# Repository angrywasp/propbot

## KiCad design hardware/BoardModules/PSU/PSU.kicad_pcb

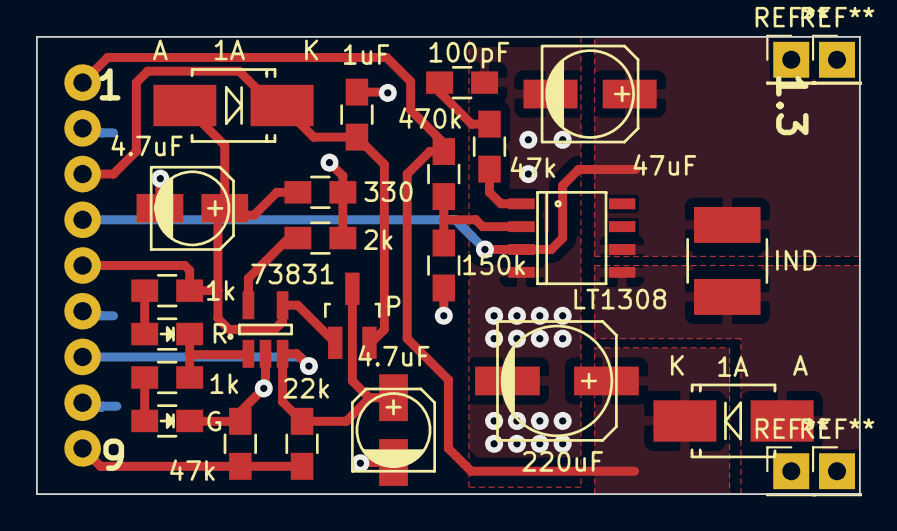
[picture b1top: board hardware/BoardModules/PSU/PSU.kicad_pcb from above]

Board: 2 copper layers, 45.7 x 25.4 mm, 27 parts (0 on the bottom side), 15 nets.

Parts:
C1, C3: 4.7uF; 4x5.3
C2: 1uF; 0805_HS
C4: 47uF; 5x5.8
C5: 100pF; 0805_HS
C6: 220uF; 6.3x7.7
D1, D2: 1A; SMB_HS
L1: IND; NR4018_HandSoldering
LED1: R; LED_0805_HS
LED2: G; LED_0805_HS
P1: INPUT; Pin_Header_Circular_1x02
P2: CONN_01X03; Pin_Header_Circular_1x03
P3: PWR_SW; Pin_Header_Circular_1x02
P4: OUTPUT; Pin_Header_Circular_1x02
Q1: P; SOT-23_HS
R1, R2: 1k; 0805_HS
R3: 2k; 0805_HS
R4: 330; 0805_HS
R5, R9: 47k; 0805_HS
R6: 150k; 0805_HS
R7: 470k; 0805_HS
R8: 22k; 0805_HS
U1: 73831; SOT-23-5_HS
U2: LT1308; SO-8

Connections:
GND: C1.2, C2.2, C3.2, C4.2, C5.2, C6.2, LED2.1, P1.2, P2.2, P4.1, R3.2, R4.1, R6.2, R9.2, U1.2, U2.4
unnamed: C1.1, D1.2, P1.1, Q1.1, R1.1, R4.2, U1.4
unnamed: C2.1, D1.1, P3.1, Q1.2
unnamed: C3.1, P2.3, Q1.3, R8.2, U1.3
unnamed: C4.1, L1.1, P3.2, U2.3, U2.6
unnamed: C5.1, R5.2
unnamed: C6.1, D2.1, P4.2, R7.1
unnamed: D2.2, L1.2, U2.5
unnamed: LED1.1, R2.1, U1.1
unnamed: LED1.2, R1.2
unnamed: LED2.2, R2.2
unnamed: P2.1, R8.1, R9.1
unnamed: R3.1, U1.5
unnamed: R5.1, U2.1
unnamed: R6.1, R7.2, U2.2

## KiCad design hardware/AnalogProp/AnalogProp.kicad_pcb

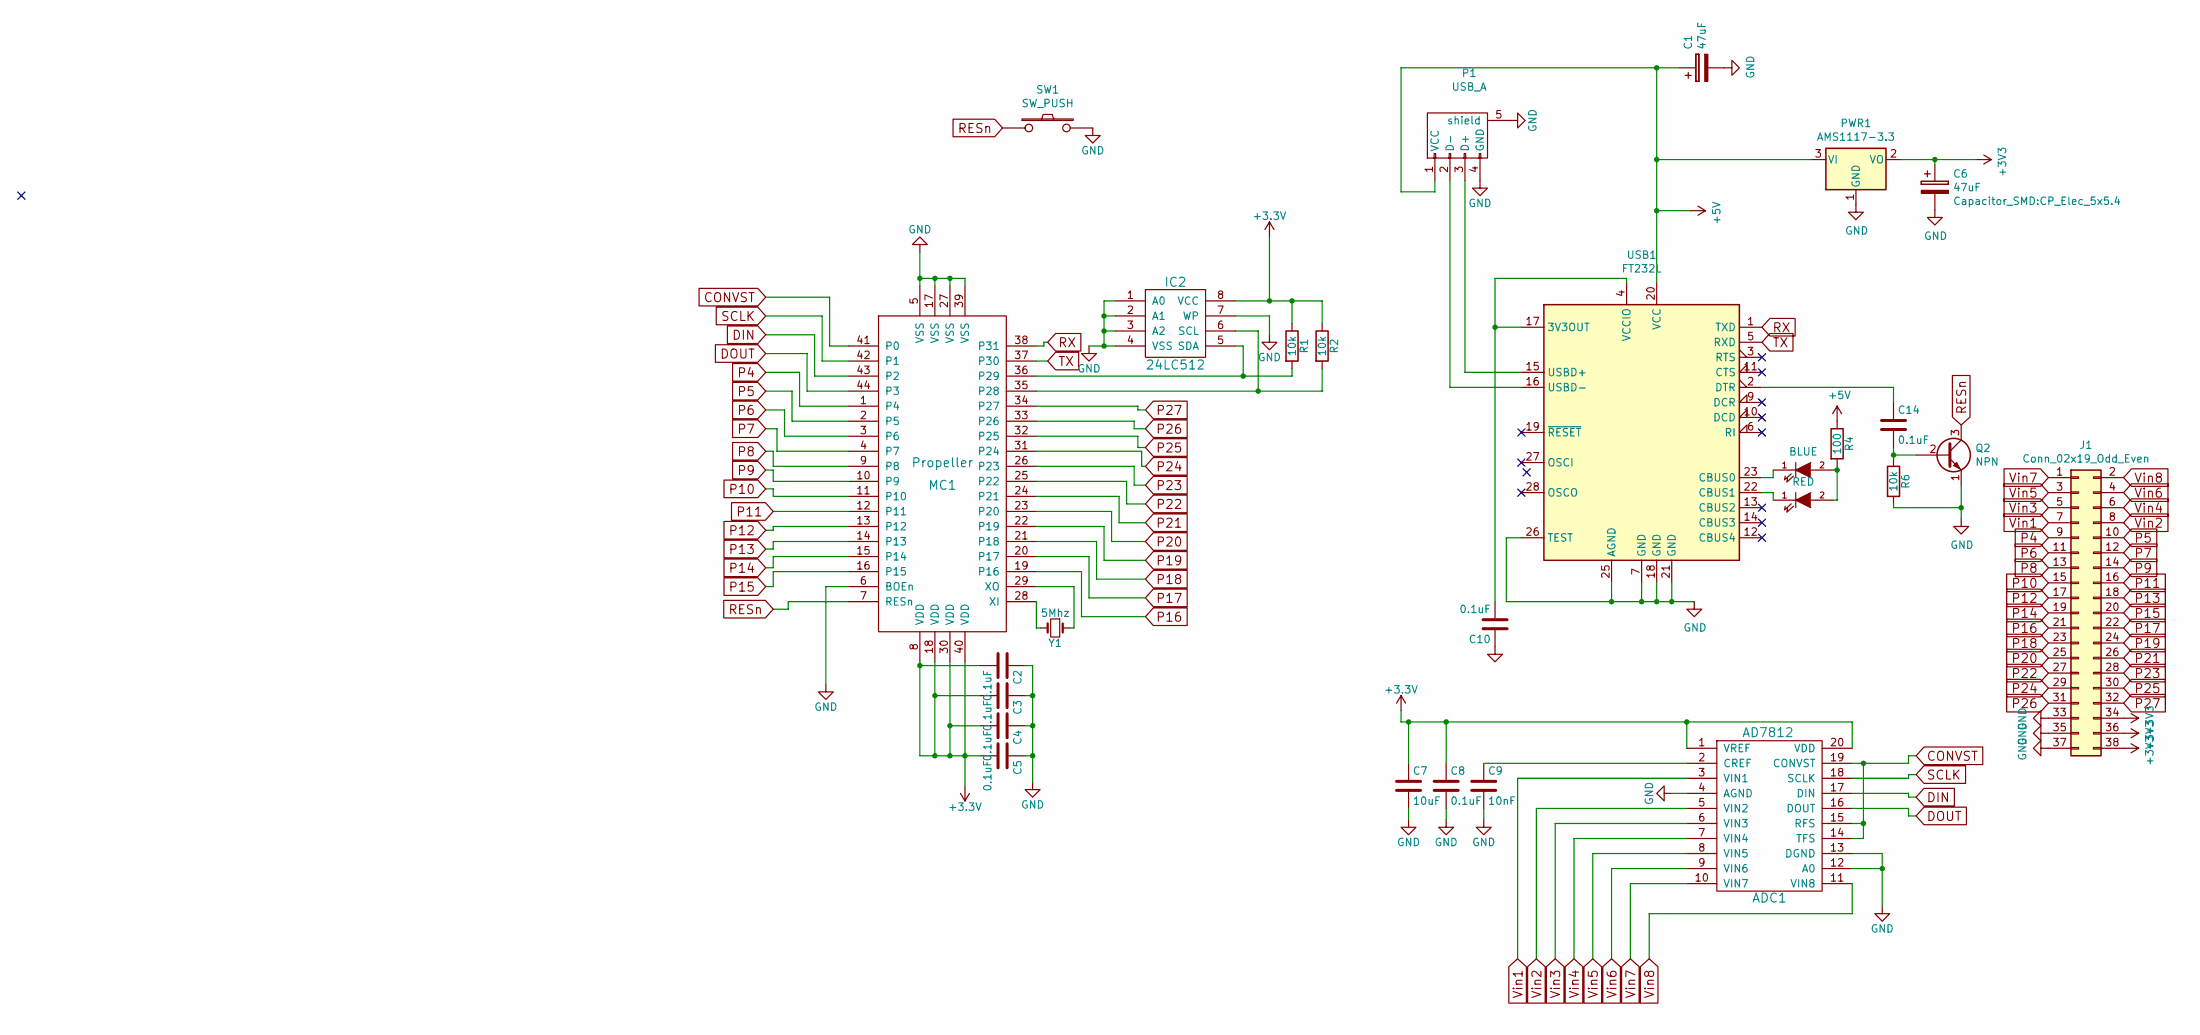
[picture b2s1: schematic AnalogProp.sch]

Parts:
ADC1: AD7812
C1, C6: 47uF; CP_Elec_5x5.4
C2, C3, C4, C5, C8, C10, C14: 0.1uF; 0805_HS
C7: 10uF; 0805_HS
C9: 10nF; 0805_HS
D2: BLUE; LED_0805_HS
D3: RED; LED_0805_HS
IC2: 24LC512; 24LC512-W
J1: Conn_02x19_Odd_Even; PinSocket_2x19_P2.54mm_Vertical
MC1: Propeller; P8X32A
P1: USB_A; USB_A_CNCTech_1001-011-01101_Horizontal
PWR1: AMS1117-3.3; SOT-223
Q2: NPN; SOT-23_HS
R1, R2, R6: 10k; 0805_HS
R4: 100; 0805_HS
SW1: SW_PUSH; SW_SPST
USB1: FT232L; SSOP-28_5.3x10.2mm_P0.65mm
Y1: 5Mhz; XTAL-2

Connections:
+5V: C1.1, P1.1 (VCC), PWR1.3 (VI), R4.1, USB1.20 (VCC); also elsewhere on the board
CONVST: ADC1.14 (TFS), ADC1.15 (RFS), ADC1.19 (CONVST), MC1.41 (P0)
DIN: ADC1.17 (DIN), MC1.43 (P2)
DOUT: ADC1.16 (DOUT), MC1.44 (P3)
GND: ADC1.4 (AGND), ADC1.12 (A0), ADC1.13 (DGND), C1.2, C2.1, C3.1, C4.1, C5.1, C6.2, C7.2, C8.2, C9.2, C10.1, IC2.1 (A0), IC2.2 (A1), IC2.3 (A2), IC2.4 (VSS), IC2.7 (WP), J1.33, J1.35, J1.37, MC1.5 (VSS), MC1.6 (BOEn), MC1.17 (VSS), MC1.27 (VSS), MC1.39 (VSS), P1.4 (GND), P1.5 (shield), PWR1.1 (GND), Q2.1 (E), R6.2, SW1.2, USB1.7 (GND), USB1.18 (GND), USB1.21 (GND), USB1.25 (AGND), USB1.26 (TEST); also elsewhere on the board
unnamed: ADC1.2 (CREF), C9.1
unnamed: C10.2, USB1.4 (VCCIO), USB1.17 (3V3OUT)
unnamed: C14.1, USB1.2 (DTR)
unnamed: C14.2, Q2.2 (B), R6.1
unnamed: D2.1 (K), USB1.23 (CBUS0)
unnamed: D2.2 (A), D3.2 (A), R4.2
unnamed: D3.1 (K), USB1.22 (CBUS1)
unnamed: IC2.5 (SDA), MC1.36 (P29), R1.2
unnamed: IC2.6 (SCL), MC1.35 (P28), R2.2
unnamed: MC1.28 (XI), Y1.2
unnamed: MC1.29 (XO), Y1.1
unnamed 16: P1.2 (D-), USB1.16 (USBD-); also elsewhere on the board
unnamed 17: P1.3 (D+), USB1.15 (USBD+); also elsewhere on the board
P4: J1.9, MC1.1 (P4)
P5: J1.10, MC1.2 (P5)
P6: J1.11, MC1.3 (P6)
P7: J1.12, MC1.4 (P7)
P8: J1.13, MC1.9 (P8)
P9: J1.14, MC1.10 (P9)
P10: J1.15, MC1.11 (P10)
P11: J1.16, MC1.12 (P11)
P12: J1.17, MC1.13 (P12)
P13: J1.18, MC1.14 (P13)
P14: J1.19, MC1.15 (P14)
P15: J1.20, MC1.16 (P15)
P16: J1.21, MC1.19 (P16)
P17: J1.22, MC1.20 (P17)
P18: J1.23, MC1.21 (P18)
P19: J1.24, MC1.22 (P19)
P20: J1.25, MC1.23 (P20)
P21: J1.26, MC1.24 (P21)
P22: J1.27, MC1.25 (P22)
P23: J1.28, MC1.26 (P23)
P24: J1.29, MC1.31 (P24)
P25: J1.30, MC1.32 (P25)
P26: J1.31, MC1.33 (P26)
P27: J1.32, MC1.34 (P27)
RESn: MC1.7 (RESn), Q2.3 (C), SW1.1
RX: MC1.38 (P31), USB1.1 (TXD)
SCLK: ADC1.18 (SCLK), MC1.42 (P1)
TX: MC1.37 (P30), USB1.5 (RXD)
Vin1: ADC1.3 (VIN1), J1.7
Vin2: ADC1.5 (VIN2), J1.8
Vin3: ADC1.6 (VIN3), J1.5
Vin4: ADC1.7 (VIN4), J1.6
Vin5: ADC1.8 (VIN5), J1.3
Vin6: ADC1.9 (VIN6), J1.4
Vin7: ADC1.10 (VIN7), J1.1
Vin8: ADC1.11 (VIN8), J1.2

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
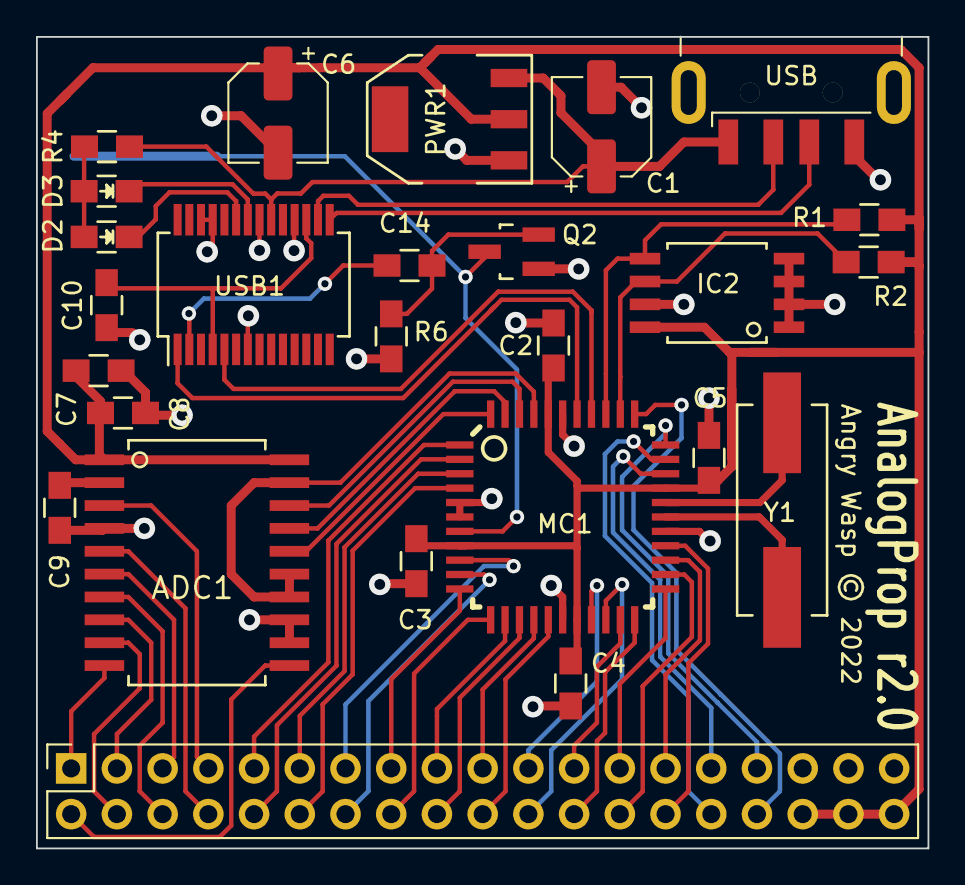
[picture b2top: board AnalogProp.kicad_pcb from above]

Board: 2 copper layers, 49.5 x 45.1 mm, 27 parts (1 on the bottom side), 55 nets.

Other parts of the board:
USB: USB_A; USB_A_CNCTech_1001-011-01101_Horizontal

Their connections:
+5V: USB.1; also elsewhere on the board
GND: USB.4, USB.5; also elsewhere on the board
unnamed 16: USB.2; also elsewhere on the board
unnamed 17: USB.3; also elsewhere on the board

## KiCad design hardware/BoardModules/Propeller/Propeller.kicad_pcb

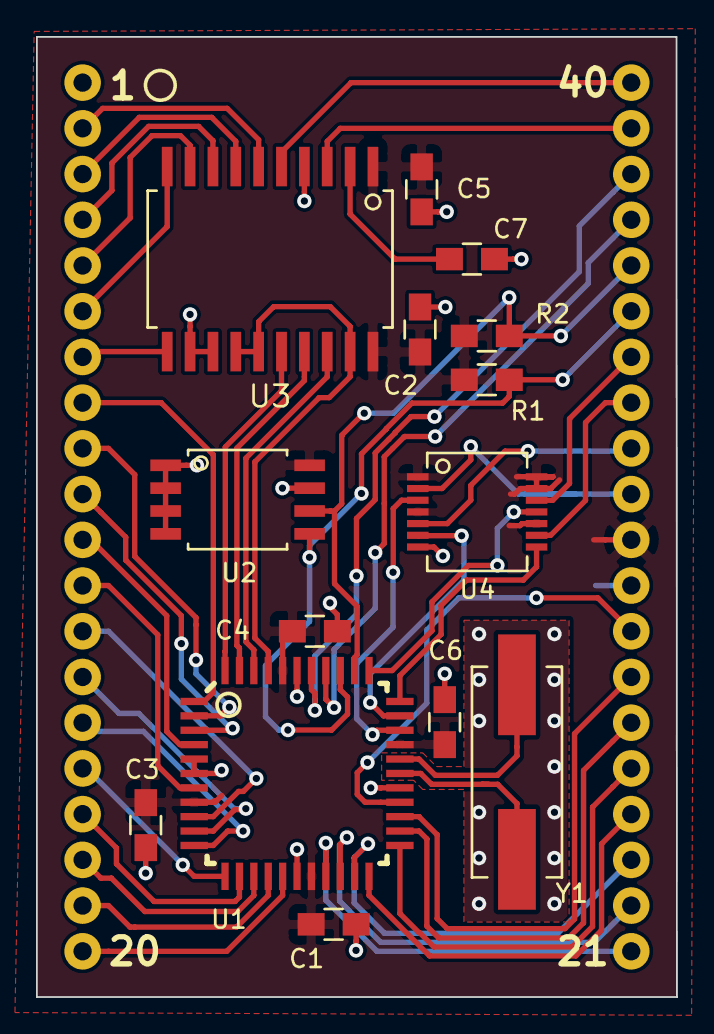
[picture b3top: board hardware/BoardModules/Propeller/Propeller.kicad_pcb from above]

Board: 2 copper layers, 35.6 x 53.3 mm, 35 parts (0 on the bottom side), 50 nets.

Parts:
C1, C2, C3, C4, C6: 0.1uF; 0805_HS
C5: 10uF; 0805_HS
C7: 10nF; 0805_HS
P1, P2, P4, P5, P6, P7, P8, P9, P10, P11, P12, P13, P14, P15, P16, P17, P18, P19, P28: CONN_01X02; Pin_Header_Circular_1x02
P3, P21: CONN_01X01; Pin_Header_Circular_1x01
R1, R2: 10k; 0805_HS
U1: Propeller; P8X32A
U2: 24LC512; 24LC512-W
U3: AD7812
U4: 74LVC126A; 74LVC126
Y1: 5Mhz; XTAL-2

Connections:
1A: P28.1, U4.2
1Y: U1.31, U4.3
2A: P28.2, U4.5
2Y: U1.32, U4.6
3A: P4.1, U4.9
3Y: U1.33, U4.8
4A: P4.2, U4.12
4Y: U1.34, U4.11
+3V3: C1.2, C2.2, C3.2, C4.2, C5.1, C6.1, P1.1, R1.1, R2.1, U1.8, U1.18, U1.30, U1.40, U2.8, U3.1, U3.20, U4.1, U4.4, U4.10, U4.13, U4.14
CONVST: U1.41, U3.14, U3.15, U3.19
DIN: U1.43, U3.17
DOUT: U1.44, U3.16
GND: C1.1, C2.1, C3.1, C4.1, C5.2, C6.2, C7.2, P1.2, U1.5, U1.6, U1.17, U1.27, U1.39, U2.1, U2.2, U2.3, U2.4, U2.7, U3.4, U3.12, U3.13, U4.7
unnamed: C7.1, U3.2
unnamed: U1.28, Y1.2
unnamed: U1.29, Y1.1
P4: P13.2, U1.1
P5: P13.1, U1.2
P6: P12.2, U1.3
P7: P12.1, U1.4
P8: P11.2, U1.9
P9: P11.1, U1.10
P10: P6.2, U1.11
P11: P6.1, U1.12
P12: P15.2, U1.13
P13: P15.1, U1.14
P14: P16.2, U1.15
P15: P16.1, U1.16
P16: P17.2, U1.19
P17: P17.1, U1.20
P18: P18.2, U1.21
P19: P18.1, U1.22
P20: P19.2, U1.23
P21: P19.1, U1.24
P22: P14.2, U1.25
P23: P14.1, U1.26
RESn: P3.1, U1.7
RX: P2.1, U1.38
SCL: P5.1, R2.2, U1.35, U2.6
SCLK: U1.42, U3.18
SDA: P5.2, R1.2, U1.36, U2.5
TX: P2.2, U1.37
Vin1: P7.2, U3.3
Vin2: P7.1, U3.5
Vin3: P8.2, U3.6
Vin4: P8.1, U3.7
Vin5: P9.1, U3.8
Vin6: P9.2, U3.9
Vin7: P10.2, U3.10
Vin8: P10.1, U3.11

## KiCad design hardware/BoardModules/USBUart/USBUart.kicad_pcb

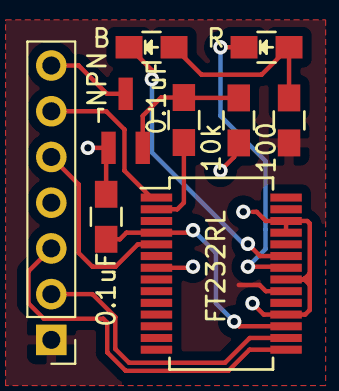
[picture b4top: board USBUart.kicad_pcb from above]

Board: 2 copper layers, 9 parts (0 on the bottom side), 13 nets.

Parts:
0.1uF, 0.1uF#2: 0.1uF; 0805_HS
10k: 10k; 0805_HS
100: 100; 0805_HS
B: BLUE; LED_0805_HS
FT232RL: FT232L; SSOP-28_5.3x10.2mm_P0.65mm
NPN: NPN; SOT-23_HS
P1: CONN_01X07; PinHeader_1x07_P2.54mm_Vertical
R: RED; LED_0805_HS

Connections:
+5V: 100.1, FT232RL.20, P1.1
GND: 0.1uF.1, 10k.2, FT232RL.7, FT232RL.18, FT232RL.21, FT232RL.25, FT232RL.26, NPN.1, P1.4
unnamed: 0.1uF.2, FT232RL.4, FT232RL.17
unnamed: 0.1uF#2.1, FT232RL.2
unnamed: 0.1uF#2.2, 10k.1, NPN.2
unnamed: B.1, FT232RL.23
unnamed: 100.2, B.2, R.2
unnamed: FT232RL.22, R.1
unnamed: FT232RL.16, P1.2
unnamed: FT232RL.15, P1.3
RESn: NPN.3, P1.7
RX: FT232RL.1, P1.6
TX: FT232RL.5, P1.5

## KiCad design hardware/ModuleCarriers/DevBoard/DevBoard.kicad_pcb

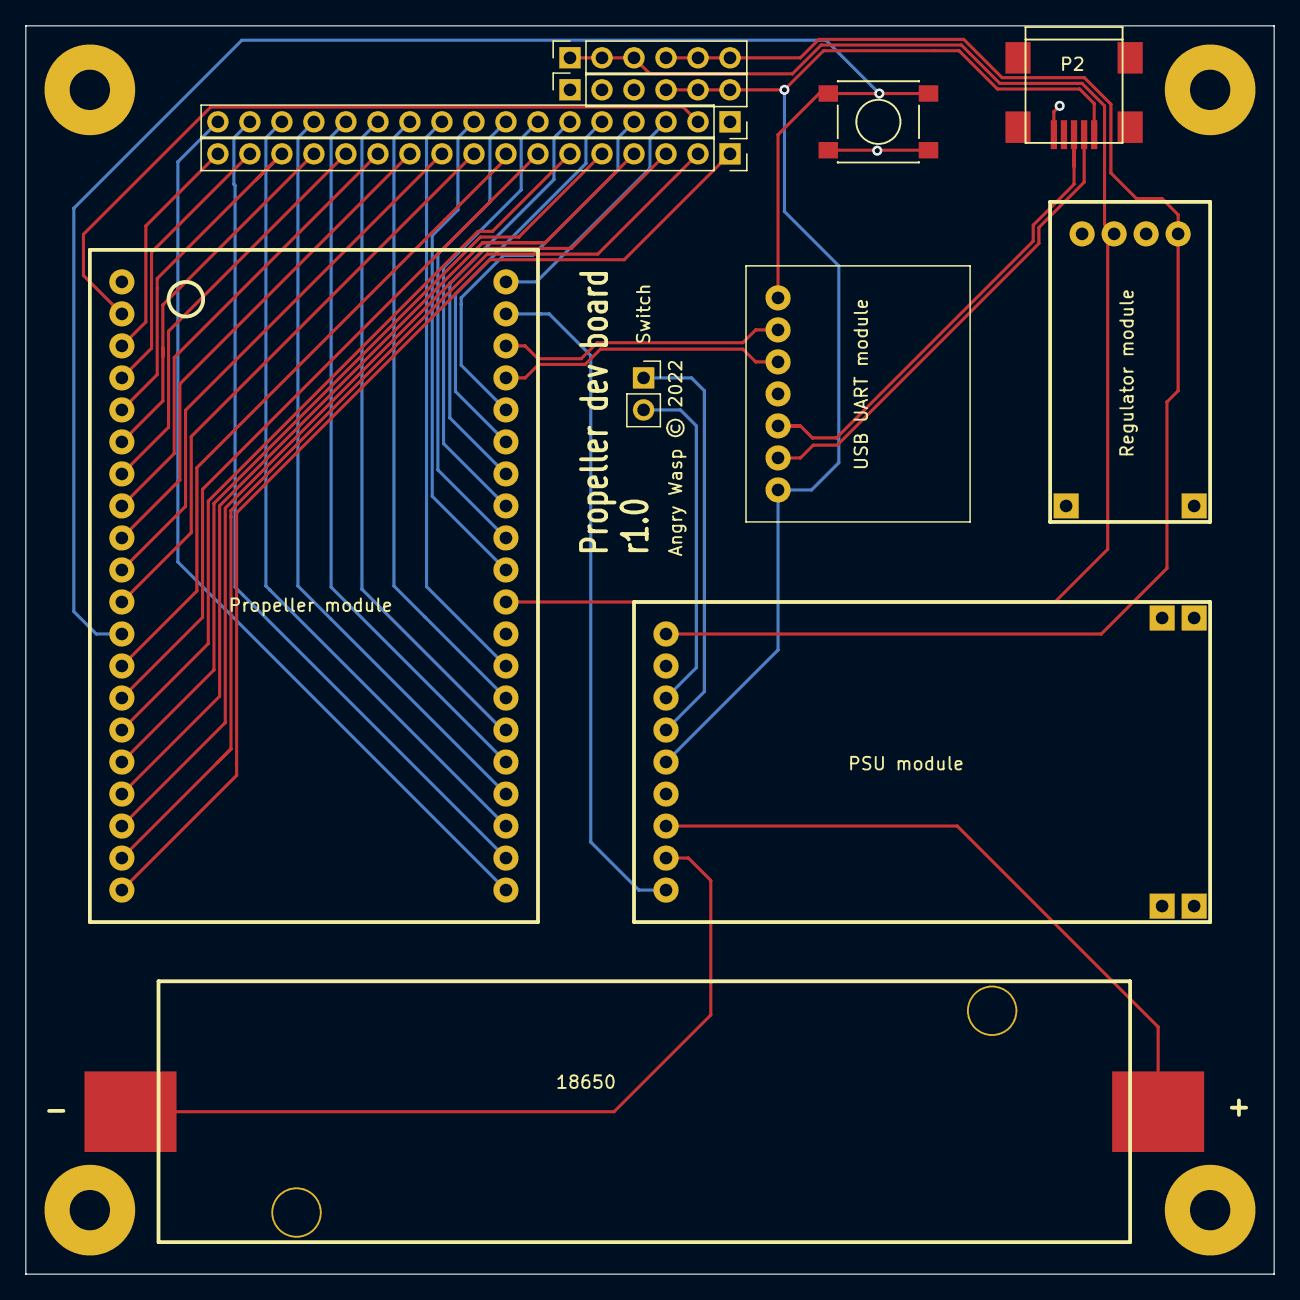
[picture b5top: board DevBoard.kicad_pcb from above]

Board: 2 copper layers, 99.1 x 99.1 mm, 16 parts (0 on the bottom side), 47 nets.

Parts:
18650: Battery; Keystone 18650
J1, J2: Conn_01x17; PinSocket_1x17_P2.54mm_Vertical
M1, M2, M3, M4: MountingHole; MountingHole-3mm
P1, P3: CONN_01X06; PinSocket_1x06_P2.54mm_Vertical
P2: USB_OTG; USB_Mini-B
PSU module: PSU
Propeller module: Prop
Regulator module: Regulator
SW1: SW_PUSH; SW_SPST
Switch: CONN_01X02; PinSocket_1x02_P2.54mm_Vertical
USB UART module: USBUart

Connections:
+3V3: P1.1, P1.2, P1.3, Propeller module.30, Regulator module.3
+5V: P2.1, P3.4, P3.5, P3.6, PSU module.5, USB UART module.1
+5VA: P1.4, P1.5, P1.6, PSU module.1, Regulator module.1
GND: P2.5, P3.1, P3.2, P3.3, PSU module.2, PSU module.6, Propeller module.29, Regulator module.2, Regulator module.4, SW1.2, USB UART module.4
unnamed: 18650.1, PSU module.7
unnamed: 18650.2, PSU module.8
unnamed: J1.1, Propeller module.20
unnamed: J1.2, Propeller module.19
unnamed: J1.3, Propeller module.18
unnamed: J1.4, Propeller module.17
unnamed: J1.5, Propeller module.16
unnamed: J1.6, Propeller module.15
unnamed: J1.7, Propeller module.14
unnamed: J1.8, Propeller module.13
unnamed: J1.9, Propeller module.11
unnamed: J1.10, Propeller module.10
unnamed: J1.11, Propeller module.9
unnamed: J1.12, Propeller module.8
unnamed: J1.13, Propeller module.7
unnamed: J1.14, Propeller module.6
unnamed: J1.15, Propeller module.5
unnamed: J1.16, Propeller module.4
unnamed: J1.17, Propeller module.3
unnamed: J2.2, Propeller module.2
unnamed: J2.3, Propeller module.40
unnamed: J2.4, Propeller module.36
unnamed: J2.5, Propeller module.35
unnamed: J2.6, Propeller module.34
unnamed: J2.7, Propeller module.33
unnamed: J2.8, Propeller module.32
unnamed: J2.9, Propeller module.31
unnamed: J2.10, Propeller module.28
unnamed: J2.11, Propeller module.27
unnamed: J2.12, Propeller module.26
unnamed: J2.13, Propeller module.25
unnamed: J2.14, Propeller module.24
unnamed: J2.15, Propeller module.23
unnamed: J2.16, Propeller module.22
unnamed: J2.17, Propeller module.21
unnamed: P2.2, USB UART module.2
unnamed: P2.3, USB UART module.3
unnamed: PSU module.4, Switch.1
unnamed: PSU module.3, Switch.2
unnamed: PSU module.9, Propeller module.39
RESn: Propeller module.12, SW1.1, USB UART module.7
RX: Propeller module.38, USB UART module.6
TX: Propeller module.37, USB UART module.5

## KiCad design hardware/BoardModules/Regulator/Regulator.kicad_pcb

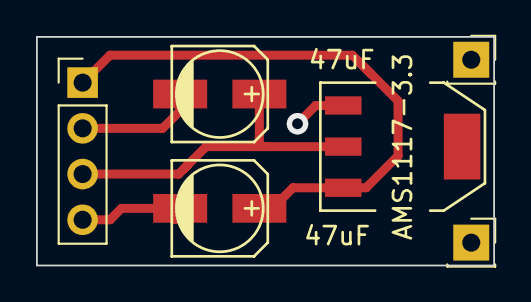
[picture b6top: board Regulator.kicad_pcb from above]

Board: 2 copper layers, 25.4 x 12.7 mm, 4 parts (0 on the bottom side), 3 nets.

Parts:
47uF: 47uf; 5x5.3
47uF#2: CP; 5x5.3
AMS1117-3.3: AMS1117-3.3; SOT-223
J1: Conn_01x04; PinHeader_1x04_P2.54mm_Vertical

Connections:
+3V3: 47uF#2.1, AMS1117-3.3.2, J1.3
+5V: 47uF.1, AMS1117-3.3.3, J1.1
GND: 47uF.2, 47uF#2.2, AMS1117-3.3.1, J1.2, J1.4

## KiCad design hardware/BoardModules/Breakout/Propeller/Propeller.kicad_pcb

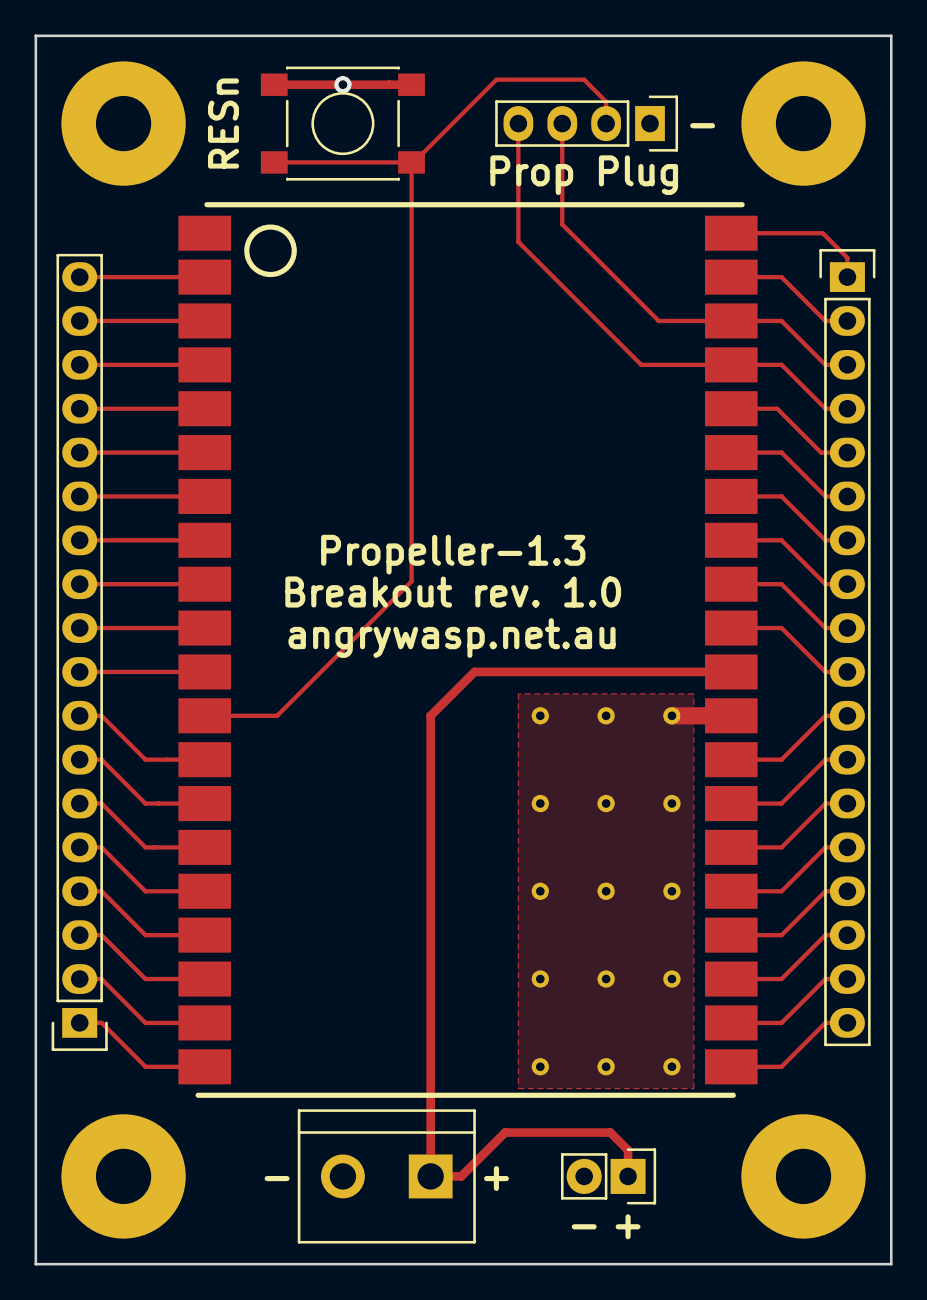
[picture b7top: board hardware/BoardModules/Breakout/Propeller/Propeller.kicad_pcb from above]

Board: 2 copper layers, 49.5 x 71.1 mm, 7 parts (0 on the bottom side), 39 nets.

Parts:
P1, P5: CONN_01X18; Pin_Header_Straight_1x18
P2: CONN_01X02; Pin_Header_Straight_1x02
P3: CONN_01X02; bornier2
P4: PROP_PLUG; Pin_Header_Straight_1x04
SW1: SW_PUSH; SW_SPST
U1: Prop-1.2

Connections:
GND: P2.2, P3.2, P4.1, SW1.1, U1.29
unnamed: P1.1, U1.20
unnamed: P1.2, U1.19
unnamed: P1.3, U1.18
unnamed: P1.4, U1.17
unnamed: P1.5, U1.16
unnamed: P1.6, U1.15
unnamed: P1.7, U1.14
unnamed: P1.8, U1.13
unnamed: P1.9, U1.11
unnamed: P1.10, U1.10
unnamed: P1.11, U1.9
unnamed: P1.12, U1.8
unnamed: P1.13, U1.7
unnamed: P1.14, U1.6
unnamed: P1.15, U1.5
unnamed: P1.16, U1.4
unnamed: P1.17, U1.3
unnamed: P1.18, U1.2
unnamed: P2.1, P3.1, U1.30
unnamed: P4.3, P5.3, U1.38
unnamed: P4.4, P5.4, U1.37
unnamed: P5.1, U1.40
unnamed: P5.2, U1.39
unnamed: P5.5, U1.36
unnamed: P5.6, U1.35
unnamed: P5.7, U1.34
unnamed: P5.8, U1.33
unnamed: P5.9, U1.32
unnamed: P5.10, U1.31
unnamed: P5.11, U1.28
unnamed: P5.12, U1.27
unnamed: P5.13, U1.26
unnamed: P5.14, U1.25
unnamed: P5.15, U1.24
unnamed: P5.16, U1.23
unnamed: P5.17, U1.22
unnamed: P5.18, U1.21
RESn: P4.2, SW1.2, U1.12

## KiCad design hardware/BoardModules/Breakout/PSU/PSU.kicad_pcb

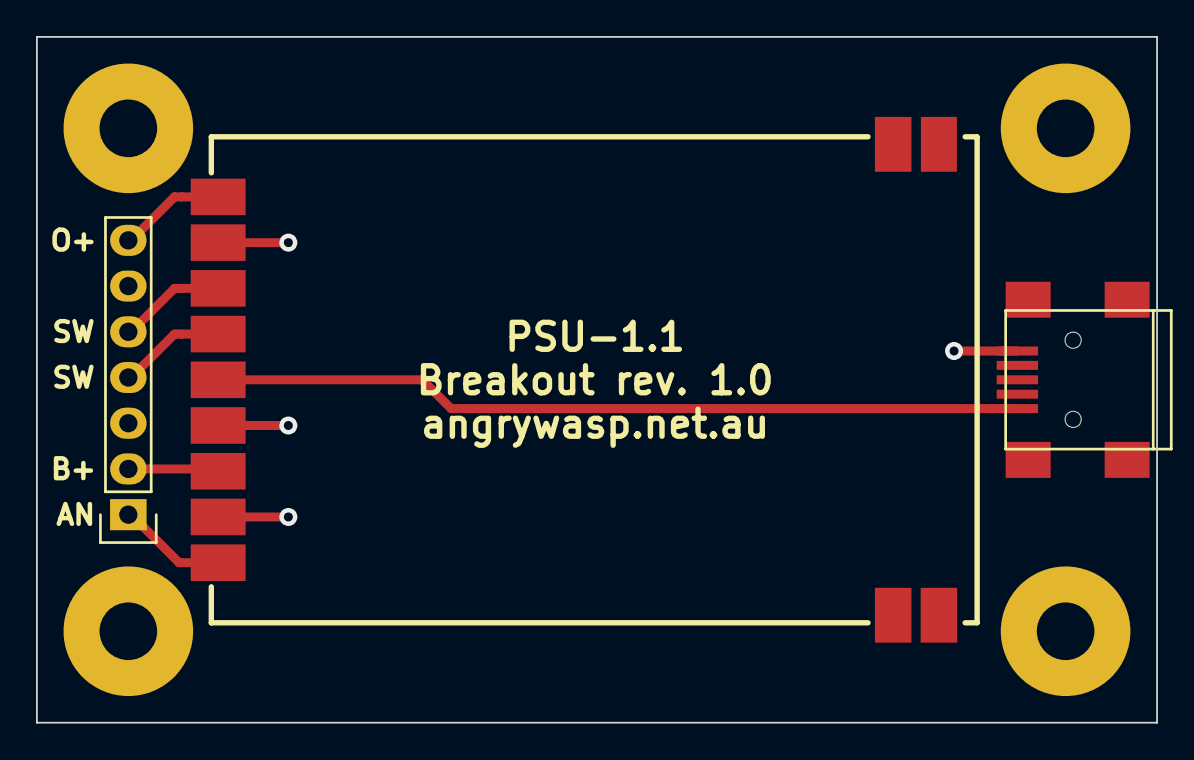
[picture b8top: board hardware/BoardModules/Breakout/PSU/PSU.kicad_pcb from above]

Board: 2 copper layers, 62.2 x 38.1 mm, 3 parts (0 on the bottom side), 7 nets.

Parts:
P1: USB_OTG; USB_Mini-B
P2: CONN_01X07; Pin_Header_Straight_1x07
U2: PSU-1.1

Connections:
GND: P1.5, P2.3, P2.6, U2.2, U2.6, U2.8
unnamed: P2.1, U2.9
unnamed: P2.2, U2.7
unnamed: P2.4, U2.4
unnamed: P2.5, U2.3
unnamed: P2.7, U2.1
USB_PWR: P1.1, U2.5

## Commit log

2022-07-30 Intellisense set up for mac
2022-07-30 SPI updates
2022-08-01 Update VS code settings
2022-08-01 Remove unnecessary includes
2022-08-01 Move sim code to simulator
2022-08-01 Add thread to simulate IO changes via keyboard
2022-08-08 Update ADC code for simulator
2022-08-08 HD44780 LCD driver
2022-08-08 LCD test program
2022-08-08 PropTool listen on port after programming
2022-08-08 Update main
2022-08-08 simulator updates
2022-08-12 Moving stuff around
2022-08-15 Add nrf24l01 driver
2022-08-15 Remove SPI library
2022-08-15 Minor updates
2022-08-18 test for thumb joystick module
2022-08-18 Adcded IO helpers for reading joystick
2022-08-18 add ssd1306 driver and test
2022-08-18 Minor fixes
2022-08-25 Updates to OLED driver
2022-08-25 Updates to ADC driver
2022-08-25 Updates to LCD driver
2022-08-25 Updates to test programs
2022-08-25 Updates to IO lib
2022-08-25 Updates to serial buffer
2022-08-25 Add lib for ushort circular buffer
2022-08-25 Program for Propbot TX
2022-08-25 schematics and board layouts for propeller and PSU systems
2022-08-30 Refactoring
2022-08-30 More hardware
2022-10-01 joystick fix
2022-10-01 basic board test program
2022-10-01 trivial updates
2022-10-01 propbot tx update
2022-10-01 add propbot rx program
2022-12-19 Update NRF24L01 tests

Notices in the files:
hardware/AnalogProp/AnalogProp.kicad_pcb:
Angry Wasp © 2022
